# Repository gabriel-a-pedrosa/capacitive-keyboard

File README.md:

# Capacitive proximity-sensing keyboard

The hardware design, in KiCad, of a keyboard with no mechanical switches. Every
key is a capacitive sensor, so the keyboard can detect a finger as it
approaches a key and not only when the key is pressed.

## How it works

Each key is a small capacitor formed by a round pad on the top copper layer and
an electrode on the bottom layer. A finger near the pad changes that
capacitance, and measuring it tells how close the finger is.

- **Key matrix.** The keys are arranged in 5 rows and 15 columns, so the whole
  layout needs only 20 lines instead of one per key.
- **Multiplexing.** Analog multiplexers (CD74HC4067 and ADG1408) connect one
  row and one column at a time, selecting a single key.
- **Measurement.** An AD7747 capacitance-to-digital converter measures the
  selected key.
- **Controller.** An ATmega32U4 drives the multiplexers, reads the AD7747
  over I²C and talks to the computer over USB-C.

## Controller board

The controller sheet holds the ATmega32U4, the USB-C port with ESD protection
and a polyfuse, the AD7747, an ISP header to reprogram the microcontroller,
decoupling, and a reset button.

## PCB

The top layer carries the round sensing pads, one per key, under a ground pour.
The bottom layer carries the second set of electrodes, one strip per line of
the matrix, and the routing to the controller in the top-right corner.

## Files

```
hardware/conjunto_teclado.kicad_pro   KiCad 8 project
hardware/*.kicad_sch                  schematic (main sheet, multiplexers, controller)
hardware/conjunto_teclado.kicad_pcb   PCB layout
hardware/schematic.pdf                full schematic as a PDF
assets/                               images for this README
```

Open the `.kicad_pro` file with [KiCad](https://www.kicad.org/) 8 or later.

## Credits

Designed by Gabriel A. Pedrosa and João P. R. Ferreira, Engineering Physics,
University of Minho.

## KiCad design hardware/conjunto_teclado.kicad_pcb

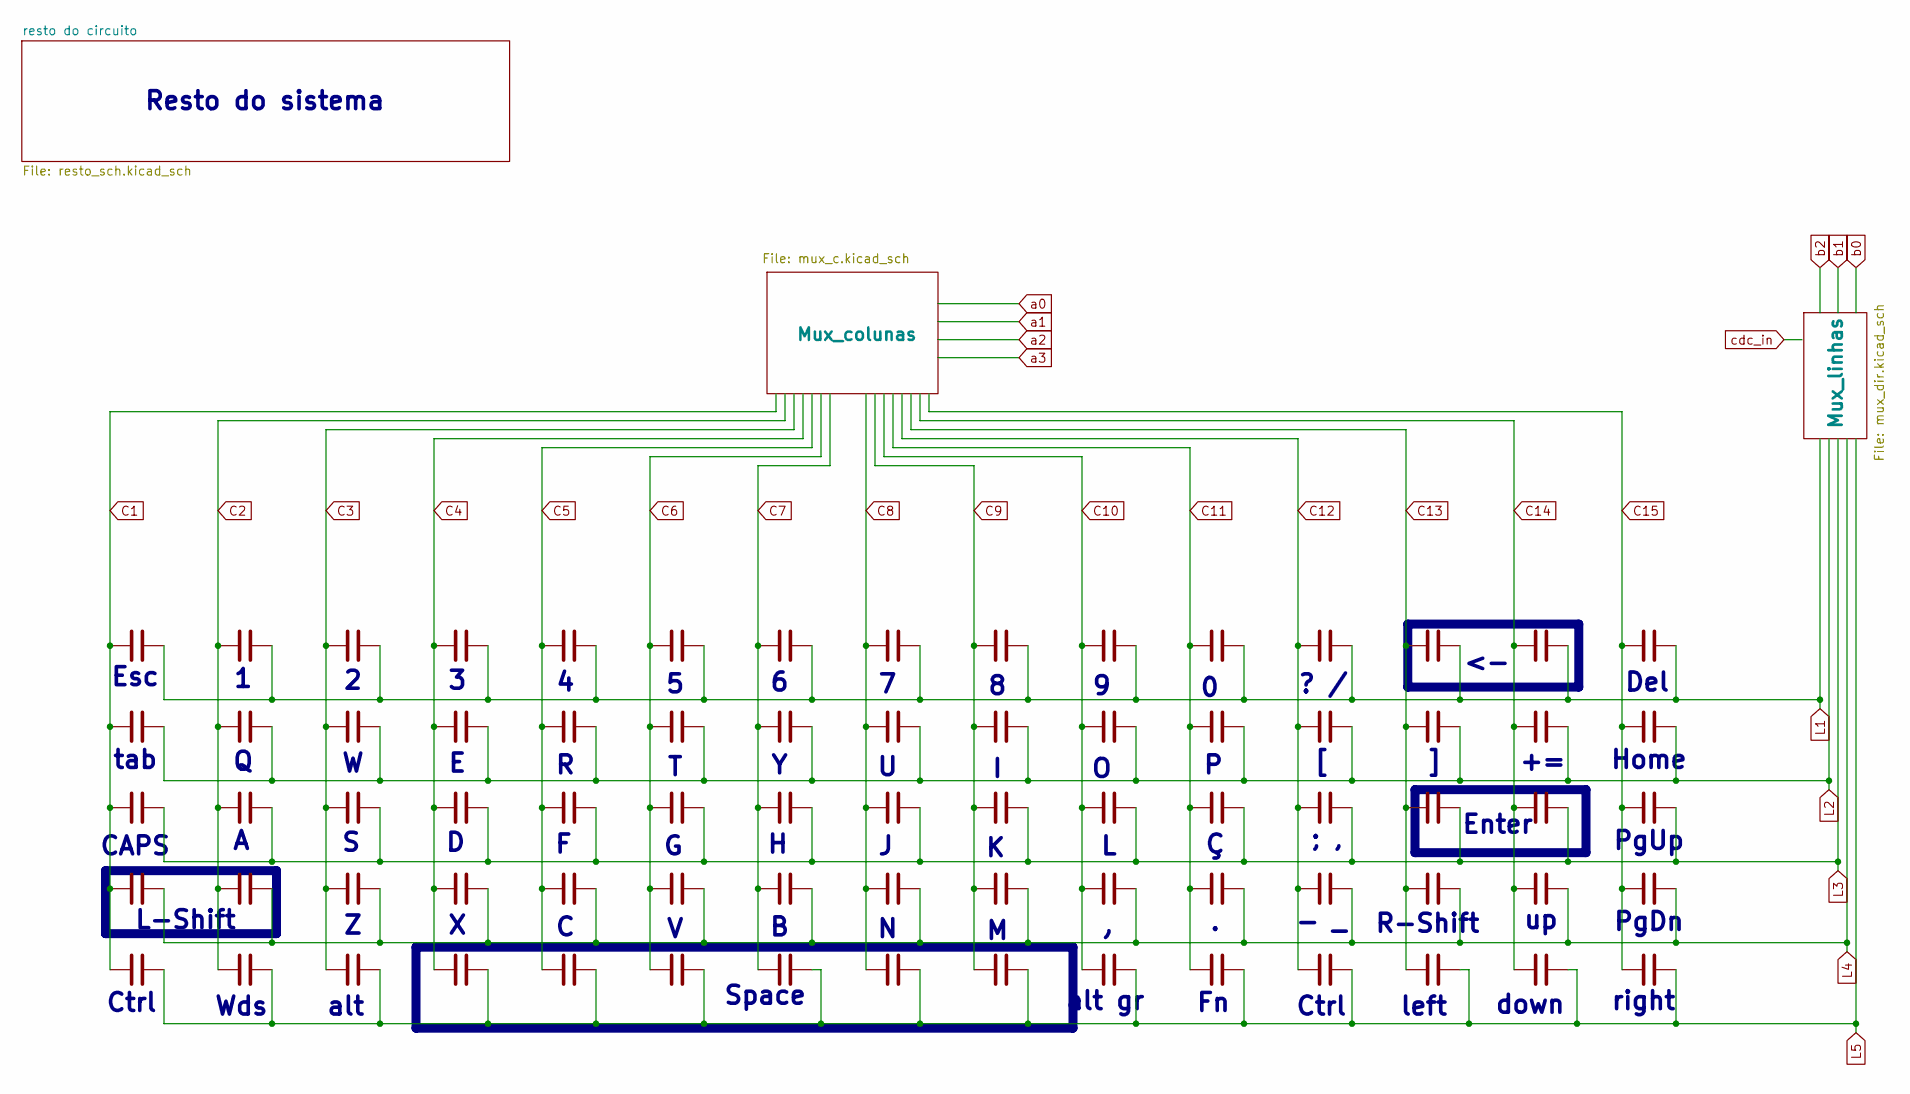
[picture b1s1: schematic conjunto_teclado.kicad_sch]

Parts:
C1, C2, C3, C4, C5, C6, C7, C8, C9, C10, C11, C12, C13, C14, C15, C16, C17, C18, C19, C20, C21, C22, C23, C24, C25, C26, C27, C28, C29, C30, C31, C32, C33, C34, C35, C36, C37, C38, C39, C40, C41, C42, C43, C44, C45, C46, C47, C48, C49, C50, C51, C52, C53, C54, C55, C56, C57, C58, C59, C60, C61, C62, C63, C64, C65, C66, C67, C68, C69, C70, C71, C72, C73, C74, C75: C; Sensor_v2

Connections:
C1: C1.1, C16.1, C31.1, C46.1, C61.1; also elsewhere on the board
C2: C2.1, C17.1, C32.1, C47.1, C62.1; also elsewhere on the board
C3: C3.1, C18.1, C33.1, C48.1, C63.1; also elsewhere on the board
C4: C4.1, C19.1, C34.1, C49.1, C64.1; also elsewhere on the board
C5: C5.1, C20.1, C35.1, C50.1, C65.1; also elsewhere on the board
C6: C6.1, C21.1, C36.1, C51.1, C66.1; also elsewhere on the board
C7: C7.1, C22.1, C37.1, C52.1, C67.1; also elsewhere on the board
C8: C8.1, C23.1, C38.1, C53.1, C68.1; also elsewhere on the board
C9: C9.1, C24.1, C39.1, C54.1, C69.1; also elsewhere on the board
C10: C10.1, C25.1, C40.1, C55.1, C70.1; also elsewhere on the board
C11: C11.1, C26.1, C41.1, C56.1, C71.1; also elsewhere on the board
C12: C12.1, C27.1, C42.1, C57.1, C72.1; also elsewhere on the board
C13: C13.1, C28.1, C43.1, C58.1, C73.1; also elsewhere on the board
C14: C14.1, C29.1, C44.1, C59.1, C74.1; also elsewhere on the board
C15: C15.1, C30.1, C45.1, C60.1, C75.1; also elsewhere on the board
L1: C1.2, C2.2, C3.2, C4.2, C5.2, C6.2, C7.2, C8.2, C9.2, C10.2, C11.2, C12.2, C13.2, C14.2, C15.2; also elsewhere on the board
L2: C16.2, C17.2, C18.2, C19.2, C20.2, C21.2, C22.2, C23.2, C24.2, C25.2, C26.2, C27.2, C28.2, C29.2, C30.2; also elsewhere on the board
L3: C31.2, C32.2, C33.2, C34.2, C35.2, C36.2, C37.2, C38.2, C39.2, C40.2, C41.2, C42.2, C43.2, C44.2, C45.2; also elsewhere on the board
L4: C46.2, C47.2, C48.2, C49.2, C50.2, C51.2, C52.2, C53.2, C54.2, C55.2, C56.2, C57.2, C58.2, C59.2, C60.2; also elsewhere on the board
L5: C61.2, C62.2, C63.2, C64.2, C65.2, C66.2, C67.2, C68.2, C69.2, C70.2, C71.2, C72.2, C73.2, C74.2, C75.2; also elsewhere on the board

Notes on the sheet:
Enter
? /
alt gr
tab
Ctrl
Home
Resto do sistema
alt
R-Shift
CAPS
L-Shift
Del
down
left
- _
; ,
Wds
PgDn
Esc
right
Space
PgUp

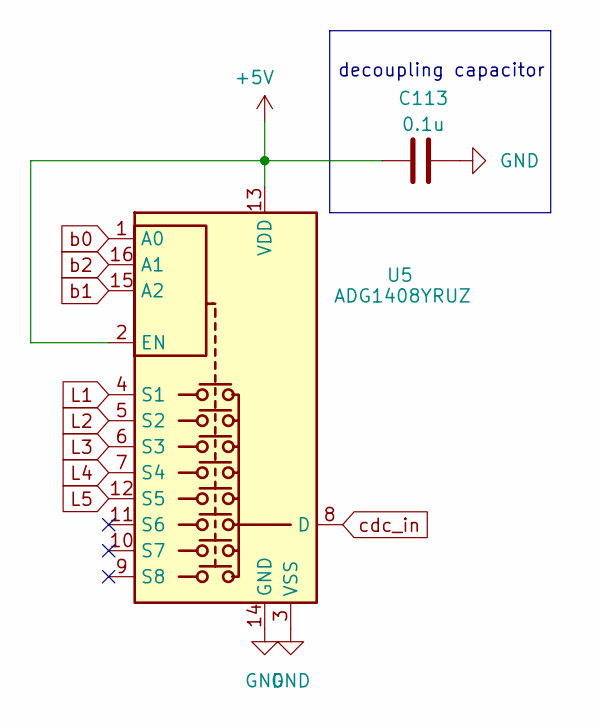
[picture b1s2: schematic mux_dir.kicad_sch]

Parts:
C113: 0.1u; C_0805_2012Metric_Pad1.18x1.45mm_HandSolder
U5: ADG1408YRUZ; TSSOP-16_4.4x5mm_P0.65mm

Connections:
+5V: C113.1, U5.2 (EN), U5.13 (VDD); also elsewhere on the board
GND: C113.2, U5.3 (VSS), U5.14 (GND); also elsewhere on the board
L1: U5.4 (S1); also elsewhere on the board
L2: U5.5 (S2); also elsewhere on the board
L3: U5.6 (S3); also elsewhere on the board
L4: U5.7 (S4); also elsewhere on the board
L5: U5.12 (S5); also elsewhere on the board
b0: U5.1 (A0); also elsewhere on the board
b1: U5.15 (A2); also elsewhere on the board
b2: U5.16 (A1); also elsewhere on the board
cdc_in: U5.8 (D); also elsewhere on the board

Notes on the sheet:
decoupling capacitor

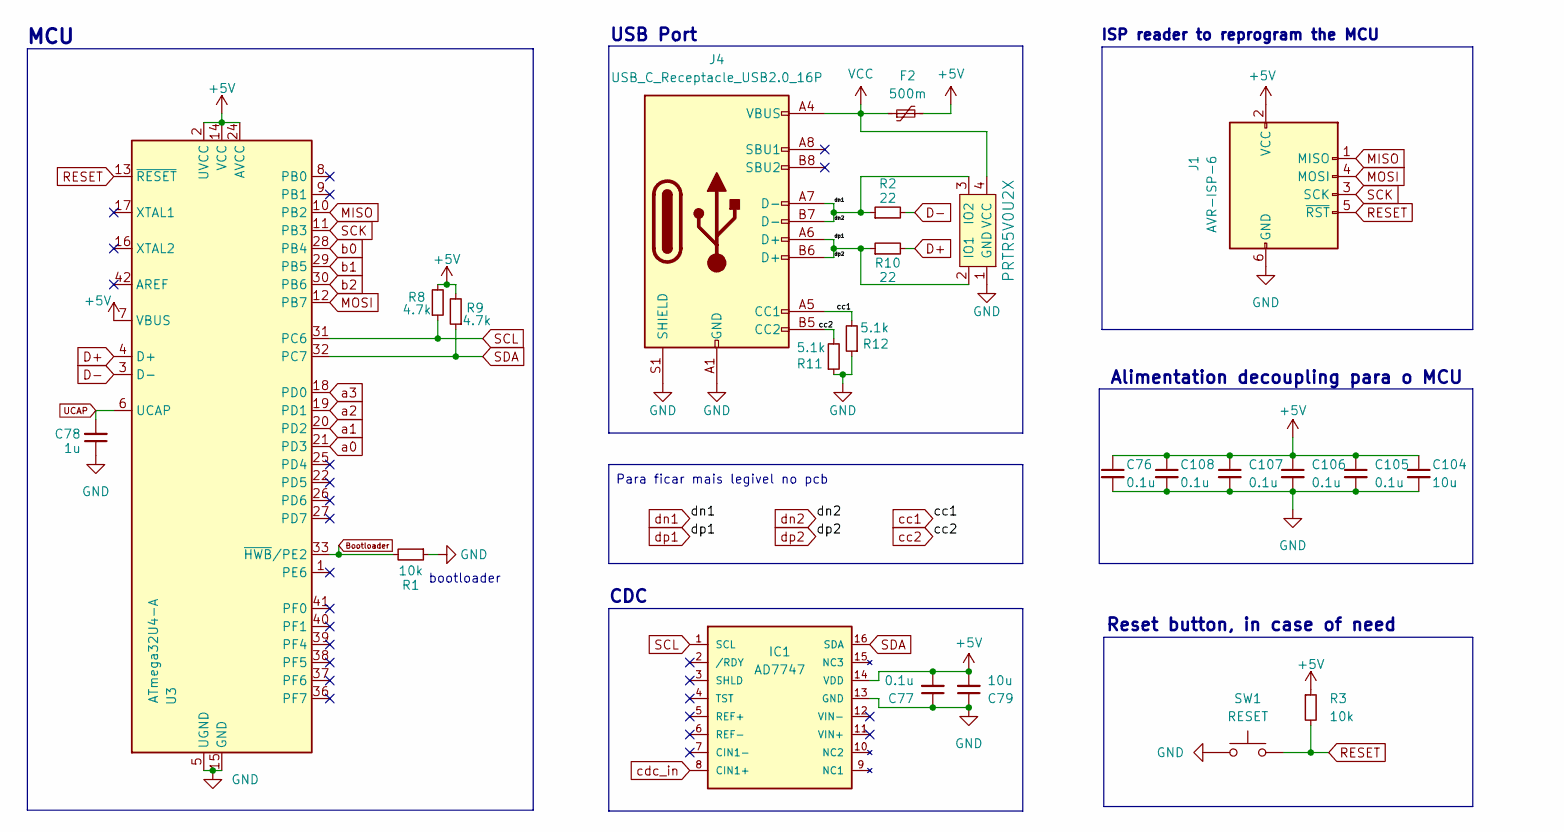
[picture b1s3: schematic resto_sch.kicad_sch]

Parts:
C76, C77, C105, C106, C107, C108: 0.1u; C_0805_2012Metric_Pad1.18x1.45mm_HandSolder
C78: 1u; C_0805_2012Metric_Pad1.18x1.45mm_HandSolder
C79: 10u; CP_EIA-2012-12_Kemet-R_Pad1.30x1.05mm_HandSolder
C104: 10u; C_0805_2012Metric_Pad1.18x1.45mm_HandSolder
F2: 500m; Fuse_1206_3216Metric
IC1: AD7747; TSSOP16
J1: AVR-ISP-6; IDC-Header_2x03_P2.54mm_Vertical_SMD
J4: USB_C_Receptacle_USB2.0_16P; USB_C_Receptacle_HRO_TYPE-C-31-M-12
R1, R3: 10k; R_0805_2012Metric_Pad1.20x1.40mm_HandSolder
R2, R10: 22; R_0805_2012Metric_Pad1.20x1.40mm_HandSolder
R8, R9: 4.7k; R_0805_2012Metric_Pad1.20x1.40mm_HandSolder
R11, R12: 5.1k; R_0805_2012Metric_Pad1.20x1.40mm_HandSolder
SW1: RESET; SW_SPST_SKQG_WithStem
U1: PRTR5V0U2X; SOT143B
U3: ATmega32U4-A; TQFP-44_10x10mm_P0.8mm

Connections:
+5V: C76.1, C77.2, C79.2, C104.1, C105.1, C106.1, C107.1, C108.1, F2.2, IC1.14 (VDD), J1.2 (VCC), R3.1, R8.2, R9.2, U3.2 (UVCC), U3.7 (VBUS), U3.14 (VCC), U3.24 (AVCC), U3.34 (VCC), U3.44 (AVCC); also elsewhere on the board
Bootloader: R1.2, U3.33 (~HWB/PE2)
D+: R10.2, U3.4 (D+)
D-: R2.2, U3.3 (D-)
GND: C76.2, C77.1, C78.1, C79.1, C104.2, C105.2, C106.2, C107.2, C108.2, IC1.13 (GND), J1.6 (GND), J4.A1 (GND), J4.A12 (GND), J4.B1 (GND), J4.B12 (GND), J4.S1 (SHIELD), R1.1, R11.1, R12.1, SW1.1, U1.1 (GND), U3.5 (UGND), U3.15 (GND), U3.23 (GND), U3.35 (GND), U3.43 (GND); also elsewhere on the board
MISO: J1.1 (MISO), U3.10 (PB2)
MOSI: J1.4 (MOSI), U3.12 (PB7)
RESET: J1.5 (~RST), R3.2, SW1.2, U3.13 (~RESET)
SCK: J1.3 (SCK), U3.11 (PB3)
SCL: IC1.1 (SCL), R8.1, U3.31 (PC6)
SDA: IC1.16 (SDA), R9.1, U3.32 (PC7)
UCAP: C78.2, U3.6 (UCAP)
VCC: F2.1, J4.A4 (VBUS), J4.A9 (VBUS), J4.B4 (VBUS), J4.B9 (VBUS), U1.4 (VCC)
a0: U3.21 (PD3); also elsewhere on the board
a1: U3.20 (PD2); also elsewhere on the board
a2: U3.19 (PD1); also elsewhere on the board
a3: U3.18 (PD0); also elsewhere on the board
b0: U3.28 (PB4); also elsewhere on the board
b1: U3.29 (PB5); also elsewhere on the board
b2: U3.30 (PB6); also elsewhere on the board
cc1: J4.A5 (CC1), R12.2
cc2: J4.B5 (CC2), R11.2
cdc_in: IC1.8 (CIN1+); also elsewhere on the board
dn1: J4.A7 (D-), J4.B7 (D-), R2.1, U1.3 (IO2)
dp1: J4.A6 (D+), J4.B6 (D+), R10.1, U1.2 (IO1)

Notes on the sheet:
bootloader
Para ficar mais legivel no pcb
CDC
USB Port
Alimentation decoupling para o MCU
Reset button, in case of need
ISP reader to reprogram the MCU
MCU

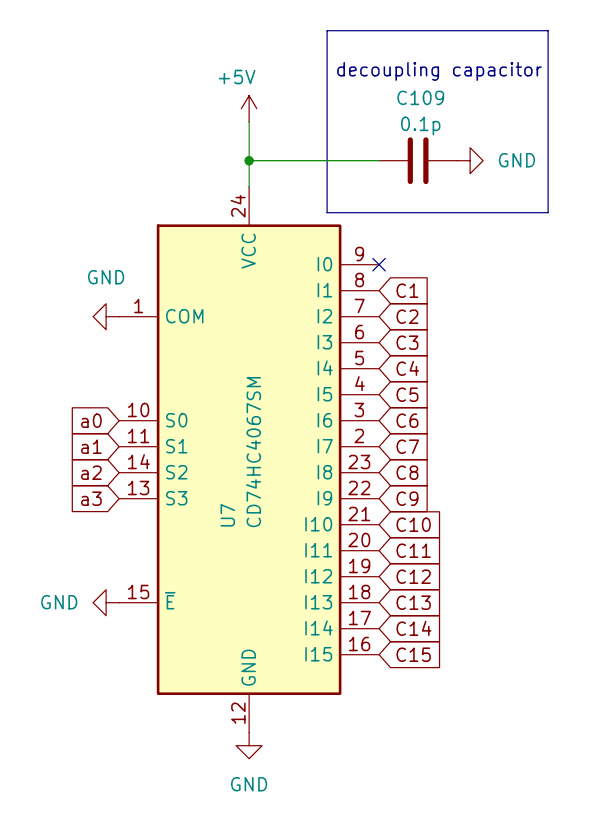
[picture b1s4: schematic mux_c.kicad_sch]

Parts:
C109: 0.1p; C_0805_2012Metric_Pad1.18x1.45mm_HandSolder
U7: CD74HC4067SM; SSOP-24_5.3x8.2mm_P0.65mm

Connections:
+5V: C109.1, U7.24 (VCC); also elsewhere on the board
C1: U7.8 (I1); also elsewhere on the board
C2: U7.7 (I2); also elsewhere on the board
C3: U7.6 (I3); also elsewhere on the board
C4: U7.5 (I4); also elsewhere on the board
C5: U7.4 (I5); also elsewhere on the board
C6: U7.3 (I6); also elsewhere on the board
C7: U7.2 (I7); also elsewhere on the board
C8: U7.23 (I8); also elsewhere on the board
C9: U7.22 (I9); also elsewhere on the board
C10: U7.21 (I10); also elsewhere on the board
C11: U7.20 (I11); also elsewhere on the board
C12: U7.19 (I12); also elsewhere on the board
C13: U7.18 (I13); also elsewhere on the board
C14: U7.17 (I14); also elsewhere on the board
C15: U7.16 (I15); also elsewhere on the board
GND: C109.2, U7.1 (COM), U7.12 (GND), U7.15 (~E); also elsewhere on the board
a0: U7.10 (S0); also elsewhere on the board
a1: U7.11 (S1); also elsewhere on the board
a2: U7.14 (S2); also elsewhere on the board
a3: U7.13 (S3); also elsewhere on the board

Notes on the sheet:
decoupling capacitor

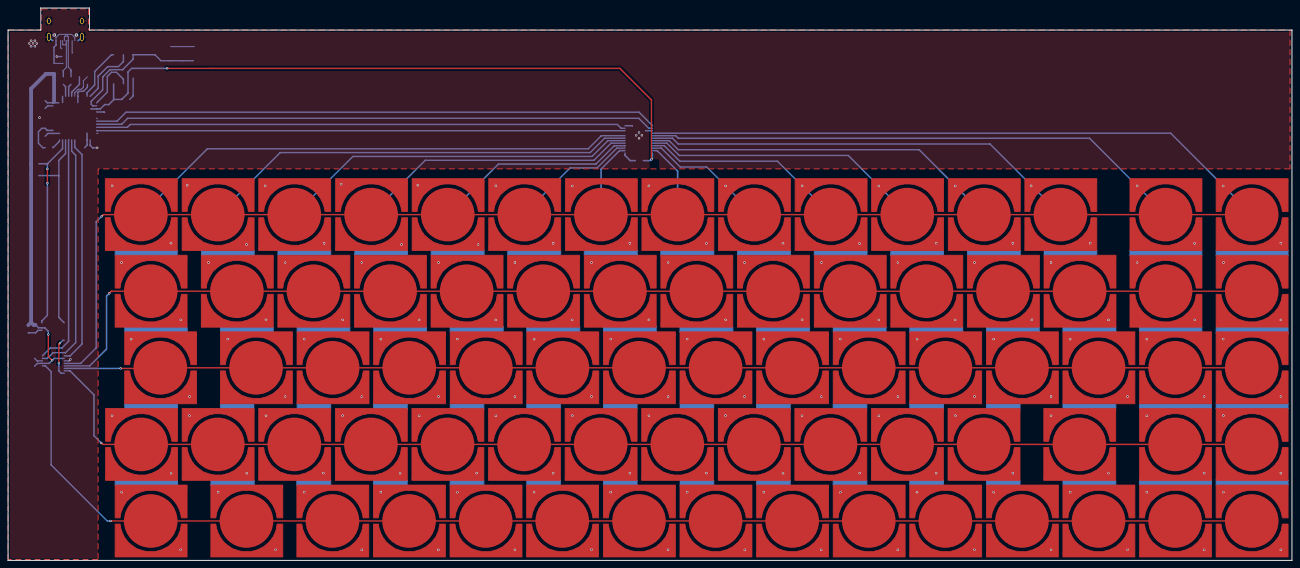
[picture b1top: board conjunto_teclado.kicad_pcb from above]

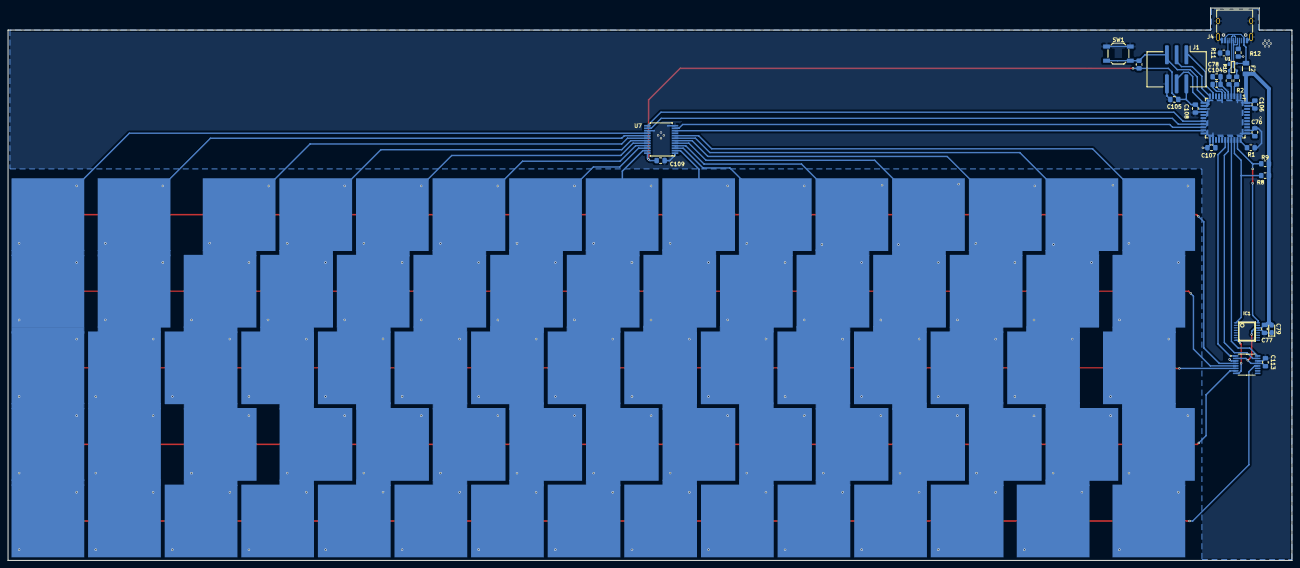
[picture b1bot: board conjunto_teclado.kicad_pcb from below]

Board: 2 copper layers, 335.3 x 144.2 mm, 103 parts (28 on the bottom side), 45 nets.
